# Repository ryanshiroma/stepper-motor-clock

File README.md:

# Stepper Clock
This project is a work in progress!! The main gial for this project was to recreate this awesome looking clock https://hackaday.com/2021/08/11/a-whole-lot-of-stepper-motors-make-the-most-graceful-7-segment-displays/ and learn about PCB design along the way!

The circuit is made up of:
- 28 stepper motors (8 segments x 4 digits = 28 parts)
- a Atmega328 for the brains
- a high precision RTC to accurate count time (plus a backup battery)
- 13 74HC595 shift registers for the stepper control pattern data
- 15 ULN2803A transistor array ICs for stepper motor driving
- 3 push buttons to set the time
- a 10A 5V power supply

The hardware for the clock will be:
- 3D printed segments
- laser cut wood board to mount the clock

## images

### Schematic and PCB
3d view

front copper

back copper

front silkscreen

### 3D Printed Parts

segment

motor mount

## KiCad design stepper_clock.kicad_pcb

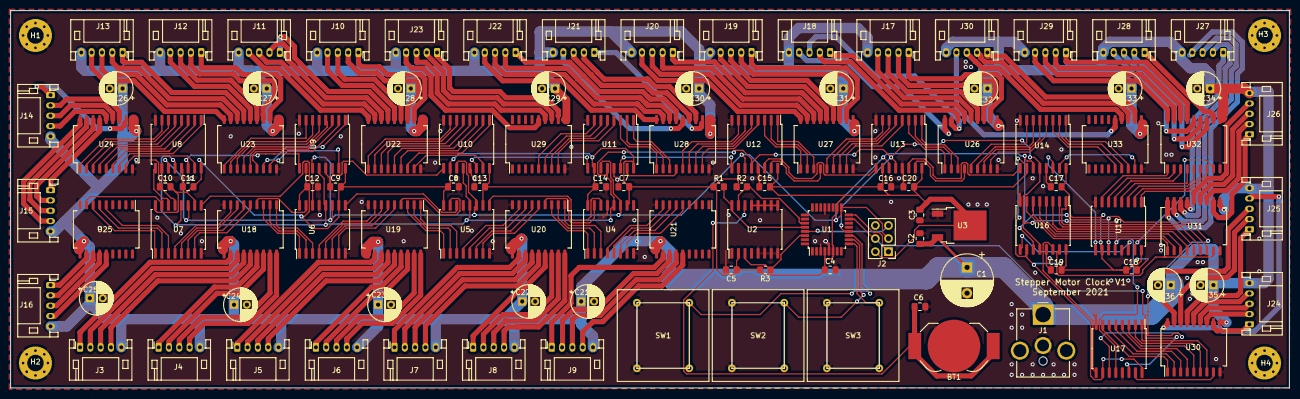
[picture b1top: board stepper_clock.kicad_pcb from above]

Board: 2 copper layers, 247.9 x 73.2 mm, 110 parts (0 on the bottom side), 252 nets.

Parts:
BT1: Battery_Cell; BatteryHolder_LINX_BAT-HLD-012-SMT
C1: 1000uF; CP_Radial_D10.0mm_P5.00mm
C2: 10uF; C_0805_2012Metric_Pad1.18x1.45mm_HandSolder
C3: 22uF; C_0805_2012Metric_Pad1.18x1.45mm_HandSolder
C4, C5, C6, C7, C8, C9, C10, C11, C12, C13, C14, C15, C16, C17, C18, C19, C20: 0.1uF; C_0805_2012Metric_Pad1.18x1.45mm_HandSolder
C21, C22, C23, C24, C25, C26, C27, C28, C29, C30, C31, C32, C33, C34, C35, C36: 100uF; CP_Radial_D6.3mm_P2.50mm
H1, H2, H3, H4: MountingHole_Pad; MountingHole_3.2mm_M3_Pad_Via
J1: Barrel_Jack; BarrelJack_CUI_PJ-063AH_Horizontal_CircularHoles
J2: ISCP; PinHeader_2x03_P2.54mm_Vertical
J3, J4, J5, J6, J7, J8, J9, J10, J11, J12, J13, J14, J15, J16, J17, J18, J19, J20, J21, J22, J23, J24, J25, J26, J27, J28, J29, J30: Conn_01x05; JST_PH_S5B-PH-K_1x05_P2.00mm_Horizontal
R1, R2, R3: 10K; R_0805_2012Metric_Pad1.20x1.40mm_HandSolder
SW1, SW2, SW3: JF15SP1H
U1: ATmega328P-AU; TQFP-32_7x7mm_P0.8mm
U2: DS3231M; SOIC-16W_7.5x10.3mm_P1.27mm
U3: AZ1117-3.3; TO-252-2
U4, U5, U6, U7, U8, U9, U10, U11, U12, U13, U14, U15, U16, U17: 74HC595; SOIC-16W_7.5x10.3mm_P1.27mm
U18, U19, U20, U21, U22, U23, U24, U25, U26, U27, U28, U29, U30, U31, U32, U33: ULN2803A; SOP-18_7x12.5mm_P1.27mm

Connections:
+3V3: C3.1, C4.1, C5.1, C7.2, C8.2, C9.2, C10.2, C11.2, C12.2, C13.2, C14.2, C15.2, C16.2, C17.2, C18.2, C19.2, C20.2, J2.2, R1.1, R2.1, R3.2, U1.4, U1.6, U1.18, U2.2, U3.2, U4.10, U4.16, U5.10, U5.16, U6.10, U6.16, U7.10, U7.16, U8.10, U8.16, U9.10, U9.16, U10.10, U10.16, U11.10, U11.16, U12.10, U12.16, U13.10, U13.16, U14.10, U14.16, U15.10, U15.16, U16.10, U16.16, U17.10, U17.16
+5V: C1.1, C2.1, C21.1, C22.1, C23.1, C24.1, C25.1, C26.1, C27.1, C28.1, C29.1, C30.1, C31.1, C32.1, C33.1, C34.1, C35.1, C36.1, J1.1, J3.5, J4.5, J5.5, J6.5, J7.5, J8.5, J9.5, J10.5, J11.5, J12.5, J13.5, J14.5, J15.5, J16.5, J17.5, J18.5, J19.5, J20.5, J21.5, J22.5, J23.5, J24.5, J25.5, J26.5, J27.5, J28.5, J29.5, J30.5, U3.3, U18.10, U19.10, U20.10, U21.10, U22.10, U23.10, U24.10, U25.10, U26.10, U27.10, U28.10, U29.10, U30.10, U31.10, U32.10, U33.10
/1HZ: R3.1, U1.30, U2.3
/CAL: SW3.1, SW3.2, U1.9
/HOUR: SW1.1, SW1.2, U1.11
/LATCH: U1.12, U4.12, U5.12, U6.12, U7.12, U8.12, U9.12, U10.12, U11.12, U12.12, U13.12, U14.12, U15.12, U16.12, U17.12
/MIN: SW2.1, SW2.2, U1.10
/MISO: J2.1, U1.16
/MOSI: J2.4, U1.15, U17.14
/RST: J2.5, U1.29
/SCK: J2.3, U1.17, U4.11, U5.11, U6.11, U7.11, U8.11, U9.11, U10.11, U11.11, U12.11, U13.11, U14.11, U15.11, U16.11, U17.11
/SCL: R1.2, U1.28, U2.16
/SDA: R2.2, U1.27, U2.15
/Shift_Registers/A1: U4.7, U21.5
/Shift_Registers/A2: U4.6, U21.6
/Shift_Registers/A3: U4.5, U21.7
/Shift_Registers/A4: U4.4, U21.8
/Shift_Registers/A5: U4.3, U20.1
/Shift_Registers/A6: U4.2, U20.2
/Shift_Registers/A7: U4.1, U20.3
/Shift_Registers/A8: U4.15, U20.4
/Shift_Registers/A9: U5.7, U20.5
/Shift_Registers/A10: U5.6, U20.6
/Shift_Registers/A11: U5.5, U20.7
/Shift_Registers/A12: U5.4, U20.8
/Shift_Registers/A13: U5.3, U19.1
/Shift_Registers/A14: U5.2, U19.2
/Shift_Registers/A15: U5.1, U19.3
/Shift_Registers/A16: U5.15, U19.4
/Shift_Registers/A17: U6.7, U19.5
/Shift_Registers/A18: U6.6, U19.6
/Shift_Registers/A19: U6.5, U19.7
/Shift_Registers/A20: U6.4, U19.8
/Shift_Registers/A21: U6.3, U18.1
/Shift_Registers/A22: U6.2, U18.2
/Shift_Registers/A23: U6.1, U18.3
/Shift_Registers/A24: U6.15, U18.4
/Shift_Registers/A25: U7.7, U18.5
/Shift_Registers/A26: U7.6, U18.6
/Shift_Registers/A27: U7.5, U18.7
/Shift_Registers/A28: U7.4, U18.8
/digit 2/A1: U7.3, U25.5
/digit 2/A2: U7.2, U25.6
/digit 2/A3: U7.1, U25.7
/digit 2/A4: U7.15, U25.8
/digit 2/A5: U8.7, U24.1
/digit 2/A6: U8.6, U24.2
/digit 2/A7: U8.5, U24.3
/digit 2/A8: U8.4, U24.4
/digit 2/A9: U8.3, U24.5
/digit 2/A10: U8.2, U24.6
/digit 2/A11: U8.1, U24.7
/digit 2/A12: U8.15, U24.8
/digit 2/A13: U9.7, U23.1
/digit 2/A14: U9.6, U23.2
/digit 2/A15: U9.5, U23.3
/digit 2/A16: U9.4, U23.4
/digit 2/A17: U9.3, U23.5
/digit 2/A18: U9.2, U23.6
/digit 2/A19: U9.1, U23.7
/digit 2/A20: U9.15, U23.8
/digit 2/A21: U10.7, U22.1
/digit 2/A22: U10.6, U22.2
/digit 2/A23: U10.5, U22.3
/digit 2/A24: U10.4, U22.4
/digit 2/A25: U10.3, U22.5
/digit 2/A26: U10.2, U22.6
/digit 2/A27: U10.1, U22.7
/digit 2/A28: U10.15, U22.8
/digit 3/A1: U11.7, U29.5
/digit 3/A2: U11.6, U29.6
/digit 3/A3: U11.5, U29.7
/digit 3/A4: U11.4, U29.8
/digit 3/A5: U11.3, U28.1
/digit 3/A6: U11.2, U28.2
/digit 3/A7: U11.1, U28.3
/digit 3/A8: U11.15, U28.4
/digit 3/A9: U12.7, U28.5
/digit 3/A10: U12.6, U28.6
/digit 3/A11: U12.5, U28.7
/digit 3/A12: U12.4, U28.8
/digit 3/A13: U12.3, U27.1
/digit 3/A14: U12.2, U27.2
/digit 3/A15: U12.1, U27.3
/digit 3/A16: U12.15, U27.4
/digit 3/A17: U13.7, U27.5
/digit 3/A18: U13.6, U27.6
/digit 3/A19: U13.5, U27.7
/digit 3/A20: U13.4, U27.8
/digit 3/A21: U13.3, U26.1
/digit 3/A22: U13.2, U26.2
/digit 3/A23: U13.1, U26.3
/digit 3/A24: U13.15, U26.4
/digit 3/A25: U14.7, U26.5
/digit 3/A26: U14.6, U26.6
/digit 3/A27: U14.5, U26.7
/digit 3/A28: U14.4, U26.8
/digit 4/A1: U14.3, U33.5
/digit 4/A2: U14.2, U33.6
/digit 4/A3: U14.1, U33.7
/digit 4/A4: U14.15, U33.8
/digit 4/A5: U15.7, U32.1
/digit 4/A6: U15.6, U32.2
/digit 4/A7: U15.5, U32.3
/digit 4/A8: U15.4, U32.4
/digit 4/A9: U15.3, U32.5
/digit 4/A10: U15.2, U32.6
/digit 4/A11: U15.1, U32.7
/digit 4/A12: U15.15, U32.8
/digit 4/A13: U16.7, U31.1
/digit 4/A14: U16.6, U31.2
/digit 4/A15: U16.5, U31.3
/digit 4/A16: U16.4, U31.4
/digit 4/A17: U16.3, U31.5
/digit 4/A18: U16.2, U31.6
/digit 4/A19: U16.1, U31.7
/digit 4/A20: U16.15, U31.8
/digit 4/A21: U17.7, U30.1
/digit 4/A22: U17.6, U30.2
/digit 4/A23: U17.5, U30.3
/digit 4/A24: U17.4, U30.4
/digit 4/A25: U17.3, U30.5
/digit 4/A26: U17.2, U30.6
/digit 4/A27: U17.1, U30.7
/digit 4/A28: U17.15, U30.8
GND: BT1.2, C1.2, C2.2, C3.2, C4.2, C5.2, C6.1, C7.1, C8.1, C9.1, C10.1, C11.1, C12.1, C13.1, C14.1, C15.1, C16.1, C17.1, C18.1, C19.1, C20.1, C21.2, C22.2, C23.2, C24.2, C25.2, C26.2, C27.2, C28.2, C29.2, C30.2, C31.2, C32.2, C33.2, C34.2, C35.2, C36.2, H1.1, H2.1, H3.1, H4.1, J1.2, J2.6, SW1.3, SW1.4, SW2.3, SW2.4, SW3.3, SW3.4, U1.3, U1.5, U1.21, U2.5, U2.6, U2.7, U2.8, U2.9, U2.10, U2.11, U2.12, U2.13, U3.1, U4.8, U4.13, U5.8, U5.13, U6.8, U6.13, U7.8, U7.13, U8.8, U8.13, U9.8, U9.13, U10.8, U10.13, U11.8, U11.13, U12.8, U12.13, U13.8, U13.13, U14.8, U14.13, U15.8, U15.13, U16.8, U16.13, U17.8, U17.13, U18.9, U19.9, U20.9, U21.9, U22.9, U23.9, U24.9, U25.9, U26.9, U27.9, U28.9, U29.9, U30.9, U31.9, U32.9, U33.9
unnamed: BT1.1, C6.2, U2.14
unnamed: J3.1, U18.11
unnamed: J3.2, U18.12
unnamed: J3.3, U18.13
unnamed: J3.4, U18.14
unnamed: J4.1, U18.15
unnamed: J4.2, U18.16
unnamed: J4.3, U18.17
unnamed: J4.4, U18.18
unnamed: J5.1, U19.11
unnamed: J5.2, U19.12
unnamed: J5.3, U19.13
unnamed: J5.4, U19.14
unnamed: J6.1, U19.15
unnamed: J6.2, U19.16
unnamed: J6.3, U19.17
unnamed: J6.4, U19.18
unnamed: J7.1, U20.11
unnamed: J7.2, U20.12
unnamed: J7.3, U20.13
unnamed: J7.4, U20.14
unnamed: J8.1, U20.15
unnamed: J8.2, U20.16
unnamed: J8.3, U20.17
unnamed: J8.4, U20.18
unnamed: J9.1, U21.11
unnamed: J9.2, U21.12
unnamed: J9.3, U21.13
unnamed: J9.4, U21.14
unnamed: J10.1, U22.11
unnamed: J10.2, U22.12
unnamed: J10.3, U22.13
unnamed: J10.4, U22.14
unnamed: J11.1, U22.15
unnamed: J11.2, U22.16
unnamed: J11.3, U22.17
unnamed: J11.4, U22.18
unnamed: J12.1, U23.11
unnamed: J12.2, U23.12
unnamed: J12.3, U23.13
unnamed: J12.4, U23.14
unnamed: J13.1, U23.15
unnamed: J13.2, U23.16
unnamed: J13.3, U23.17
unnamed: J13.4, U23.18
unnamed: J14.1, U24.11
unnamed: J14.2, U24.12
unnamed: J14.3, U24.13
unnamed: J14.4, U24.14
unnamed: J15.1, U24.15
unnamed: J15.2, U24.16
unnamed: J15.3, U24.17
unnamed: J15.4, U24.18
unnamed: J16.1, U25.11
unnamed: J16.2, U25.12
unnamed: J16.3, U25.13
unnamed: J16.4, U25.14
unnamed: J17.1, U26.11
unnamed: J17.2, U26.12
unnamed: J17.3, U26.13
unnamed: J17.4, U26.14
unnamed: J18.1, U26.15
unnamed: J18.2, U26.16
unnamed: J18.3, U26.17
unnamed: J18.4, U26.18
unnamed: J19.1, U27.11
unnamed: J19.2, U27.12
unnamed: J19.3, U27.13
unnamed: J19.4, U27.14
unnamed: J20.1, U27.15
unnamed: J20.2, U27.16
unnamed: J20.3, U27.17
unnamed: J20.4, U27.18
unnamed: J21.1, U28.11
unnamed: J21.2, U28.12
unnamed: J21.3, U28.13
unnamed: J21.4, U28.14
unnamed: J22.1, U28.15
unnamed: J22.2, U28.16
unnamed: J22.3, U28.17
unnamed: J22.4, U28.18
unnamed: J23.1, U29.11
unnamed: J23.2, U29.12
unnamed: J23.3, U29.13
unnamed: J23.4, U29.14
unnamed: J24.1, U30.11
unnamed: J24.2, U30.12
unnamed: J24.3, U30.13
unnamed: J24.4, U30.14
unnamed: J25.1, U30.15
unnamed: J25.2, U30.16
unnamed: J25.3, U30.17
unnamed: J25.4, U30.18
unnamed: J26.1, U31.11
unnamed: J26.2, U31.12
unnamed: J26.3, U31.13
unnamed: J26.4, U31.14
unnamed: J27.1, U31.15
unnamed: J27.2, U31.16
unnamed: J27.3, U31.17
unnamed: J27.4, U31.18
unnamed: J28.1, U32.11
unnamed: J28.2, U32.12
unnamed: J28.3, U32.13
unnamed: J28.4, U32.14
unnamed: J29.1, U32.15
unnamed: J29.2, U32.16
unnamed: J29.3, U32.17
unnamed: J29.4, U32.18
unnamed: J30.1, U33.11
unnamed: J30.2, U33.12
unnamed: J30.3, U33.13
unnamed: J30.4, U33.14
unnamed: U4.14, U5.9
unnamed: U5.14, U6.9
unnamed: U6.14, U7.9
unnamed: U7.14, U8.9
unnamed: U8.14, U9.9
unnamed: U9.14, U10.9
unnamed: U10.14, U11.9
unnamed: U11.14, U12.9
unnamed: U12.14, U13.9
unnamed: U13.14, U14.9
unnamed: U14.14, U15.9
unnamed: U15.14, U16.9
unnamed: U16.14, U17.9

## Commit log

2021-09-30 reorganized
2021-09-30 fixed
2021-11-16 v2 board
